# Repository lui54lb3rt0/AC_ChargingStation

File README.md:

⚠️ WARNING — READ BEFORE USE

This Arduino Uno code and Shield are provided as a starter project for educational purposes only. They are intended to help you learn about EV charging concepts and are sufficient to demonstrate basic charging station functionality. This project is not compliant with safety standards or certifications required for production use.

ELECTRICAL HAZARD: Working with AC mains power is dangerous and can result in serious injury, death, electric shock, fire, or property damage. If you are not experienced with high-voltage electrical systems, consult a licensed electrician before attempting to build or test this project.

By using this code and hardware, you accept full responsibility for your safety and any consequences that may arise.

This is a repository for a learning and development project (not a finished product).
This repository contains:
- Code for Arduino Uno to work as an EV AC Charging Station.
- KiCAD Schematic and PCB of a Shield for Arduino Uno to make the hardware for an EV AC Charging Station.
- Gerber files to fabricate the Shield.
- BOM to assemble the Shield.

There are two versions:
- V2.2: Arduino Uno shield with a fixed charging current (`EVSE_V2_2.*`, firmware in `src/uno`). This is the version the course below is based on.
- V3.0: Seeed XIAO ESP32S3 + Wio-SX1262 LoRa kit, where a second, identical kit sets the available current remotely (`EVSE_V3_0.*`, firmware in `src/station` and `src/remote`). The schematic is done, the PCB layout is not. See [docs/ESP32_LoRa_Upgrade.md](docs/ESP32_LoRa_Upgrade.md).

Instructions to execute this learning project: https://www.udemy.com/course/electric-vehicle-charging-from-theory-to-practice/?referralCode=AC67637479A66E6618A2

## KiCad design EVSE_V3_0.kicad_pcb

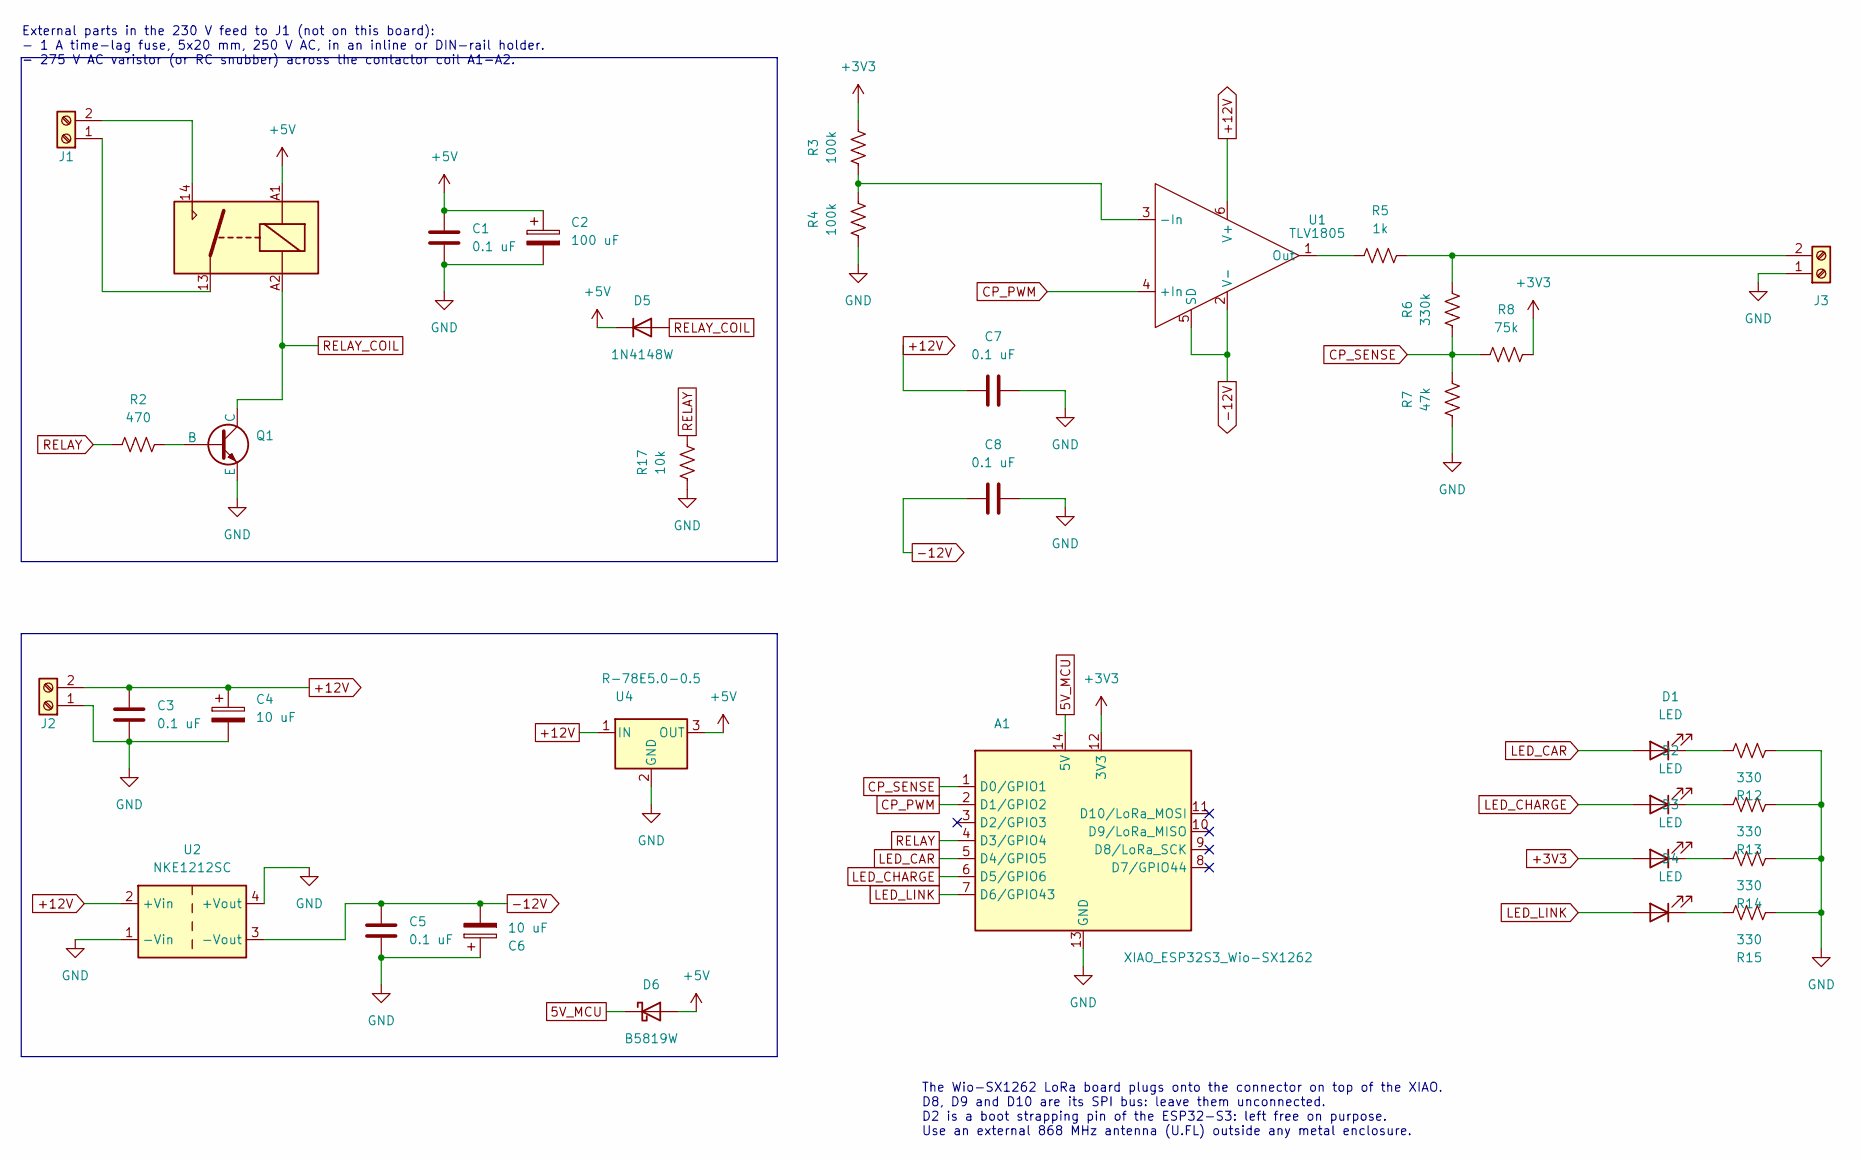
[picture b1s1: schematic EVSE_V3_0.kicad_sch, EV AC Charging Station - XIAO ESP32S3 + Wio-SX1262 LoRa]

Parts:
A1: XIAO_ESP32S3_Wio-SX1262
C1, C3, C5, C7, C8: 0.1 uF; C_1206_3216Metric
C2: 100 uF; CP_Radial_D6.3mm_P2.50mm
C4, C6: 10 uF; CP_Radial_D4.0mm_P1.50mm
D1, D2, D3, D4: LED; LED_1206_3216Metric
D5: 1N4148W; D_SOD-123
D6: B5819W; D_SOD-123
J1: CONTACTOR; Lever 2 - 2,5 2-5,0
J2: 12V_IN; Lever 2 - 2,5 2-5,0
J3: CP_PE; Lever 2 - 2,5 2-5,0
K1: Relay_SPST-NO; Relay_TE_SPST_16A
Q1: NPN; TO-92_3
R2: 470; R_1206_3216Metric
R3, R4: 100k; R_1206_3216Metric
R5: 1k; R_1206_3216Metric
R6: 330k; R_1206_3216Metric
R7: 47k; R_1206_3216Metric
R8: 75k; R_1206_3216Metric
R12, R13, R14, R15: 330; R_1206_3216Metric
R17: 10k; R_1206_3216Metric
U1: TLV1805; SOT-23-6
U2: NKE1212SC
U4: R-78E5.0-0.5; Converter_DCDC_RECOM_R-78E-0.5_THT

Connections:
5V_MCU: A1.14 (5V), D6.1 (K)
+3V3: A1.12 (3V3), D3.2 (A), R3.2, R8.2
+5V: C1.1, C2.1, D5.1 (K), D6.2 (A), K1.A1, U4.3 (OUT)
+12V: C3.1, C4.1, C7.1, J2.2, U1.6 (V+), U2.2 (+Vin), U4.1 (IN)
-12V: C5.1, C6.2, C8.1, U1.2 (V-), U1.5 (SD), U2.3 (-Vout)
CP_PWM: A1.2 (D1/GPIO2), U1.4 (+In)
CP_SENSE: A1.1 (D0/GPIO1), R6.1, R7.2, R8.1
GND: A1.13 (GND), C1.2, C2.2, C3.2, C4.2, C5.2, C6.1, C7.2, C8.2, J2.1, J3.1, Q1.3 (E), R4.1, R7.1, R12.1, R13.1, R14.1, R15.1, R17.1, U2.1 (-Vin), U2.4 (+Vout), U4.2 (GND)
LED_CAR: A1.5 (D4/GPIO5), D1.2 (A)
LED_CHARGE: A1.6 (D5/GPIO6), D2.2 (A)
LED_LINK: A1.7 (D6/GPIO43), D4.2 (A)
unnamed: D1.1 (K), R12.2
unnamed: D2.1 (K), R13.2
unnamed: D3.1 (K), R14.2
unnamed: D4.1 (K), R15.2
unnamed: J1.1, K1.13
unnamed: J1.2, K1.14
unnamed: J3.2, R5.2, R6.2
unnamed: Q1.2 (B), R2.2
unnamed: R3.1, R4.2, U1.3 (-In)
unnamed: R5.1, U1.1 (Out)
RELAY: A1.4 (D3/GPIO4), R2.1, R17.2
RELAY_COIL: D5.2 (A), K1.A2, Q1.1 (C)

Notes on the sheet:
The Wio-SX1262 LoRa board plugs onto the connector on top of the XIAO. D8, D9 and D10 are its SPI bus: leave them unconnected. D2 is a boot strapping pin of the ESP32-S3: left free on purpose. Use an external 868 MHz antenna (U.FL) outside any metal enclosure.
External parts in the 230 V feed to J1 (not on this board): - 1 A time-lag fuse, 5x20 mm, 250 V AC, in an inline or DIN-rail holder. - 275 V AC varistor (or RC snubber) across the contactor coil A1-A2.

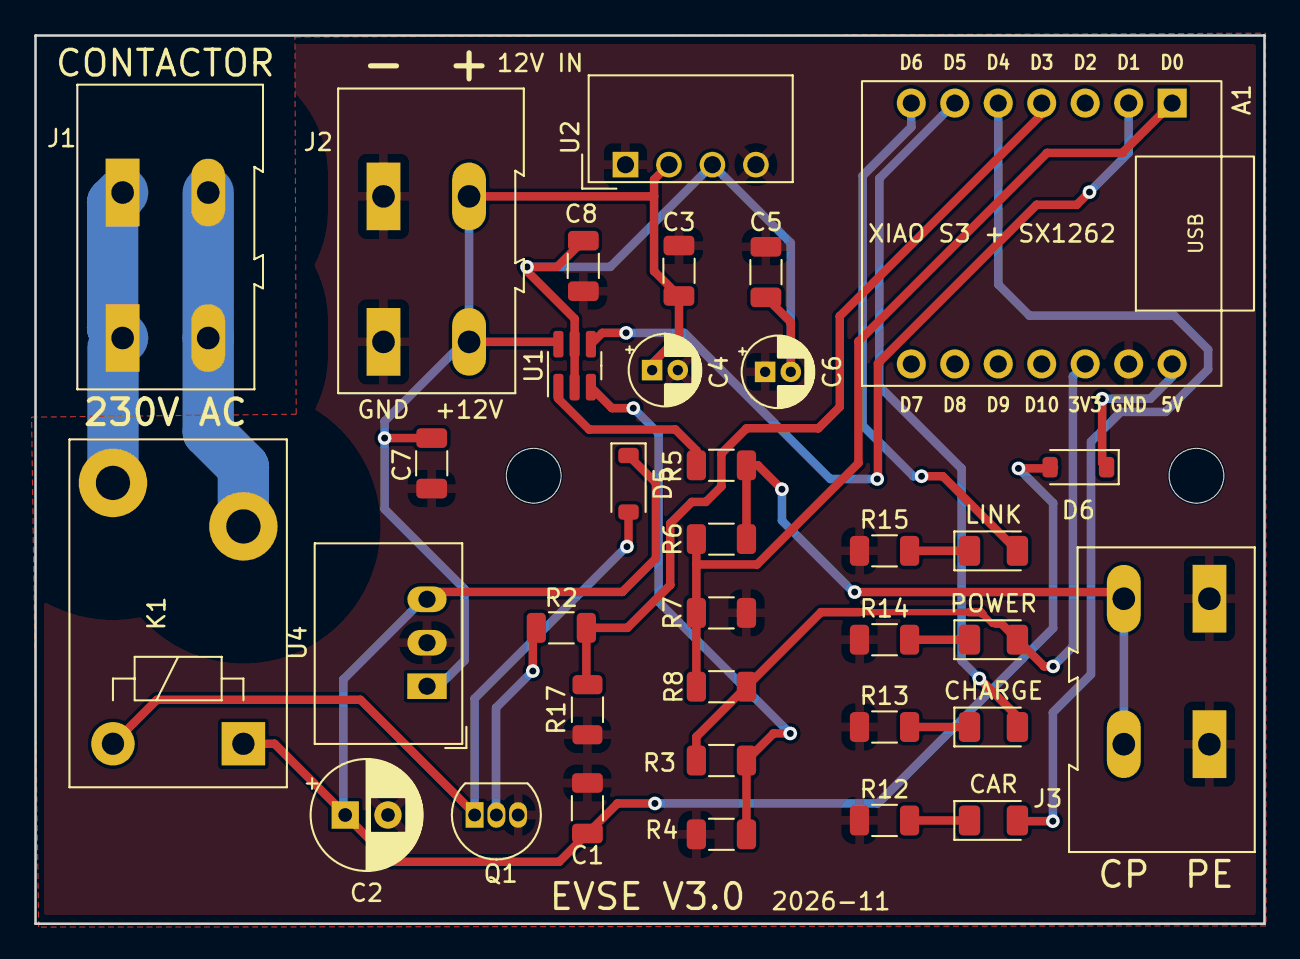
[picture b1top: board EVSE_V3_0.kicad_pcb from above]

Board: 2 copper layers, 71.8 x 51.9 mm, 37 parts (0 on the bottom side), 23 nets.

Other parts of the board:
H1, H2: MountingHole_3.2mm_M3

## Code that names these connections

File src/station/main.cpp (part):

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#define PIN_CP_IN       1   // D0, ADC - Control Pilot voltage, through the R6/R7/R8 divider
#define PIN_CP_OUT      2   // D1 - 1 kHz PWM to the comparator that drives the Control Pilot
//                      3   // D2 - strapping pin of the ESP32-S3: leave unconnected
#define PIN_RELAY       4   // D3 - HIGH = relay closed (drives the external contactor)
#define PIN_LED_CAR     5   // D4 - LED D1: car connected
#define PIN_LED_CHARGE  6   // D5 - LED D2: blinks while charging
#define PIN_LED_LINK    43  // D6 - LED D4: LoRa link ok (flickers at reset: boot log pin)
//                      44  // D7 - free
// LED D3 (power) is wired straight to 3V3 and needs no pin.

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// ------------------------------------------------------------ Setup --------
void setup() {
  // Relay first, so the contactor is guaranteed open while everything else starts.
  pinMode(PIN_RELAY, OUTPUT);
  digitalWrite(PIN_RELAY, LOW);

  pinMode(PIN_LED_CAR, OUTPUT);
  pinMode(PIN_LED_CHARGE, OUTPUT);
  pinMode(PIN_LED_LINK, OUTPUT);
  pinMode(PIN_WIO_LED, OUTPUT);
  digitalWrite(PIN_LED_CAR, LOW);
  digitalWrite(PIN_LED_CHARGE, LOW);
  digitalWrite(PIN_LED_LINK, LOW);
  digitalWrite(PIN_WIO_LED, LOW);

  Serial.begin(115200);
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      cpWrite(0);
      break;
  }
  digitalWrite(PIN_RELAY, relayOn ? HIGH : LOW);

  bool blinkSlow = (now / 500) % 2;
  bool blinkFast = (now / 125) % 2;
  if (state == 'f') {
    digitalWrite(PIN_LED_CAR, blinkFast);
    digitalWrite(PIN_LED_CHARGE, !blinkFast);
  } else {
    digitalWrite(PIN_LED_CAR, state != 'a');
    // Blinking: charging. Steady: car wants power but charging is paused.
    digitalWrite(PIN_LED_CHARGE, state == 'c' && (relayOn ? blinkSlow : true));
  }
  digitalWrite(PIN_LED_LINK, linkAlive());
  digitalWrite(PIN_WIO_LED, linkAlive());  // same, on the LoRa board itself

  // ---- Debug output
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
